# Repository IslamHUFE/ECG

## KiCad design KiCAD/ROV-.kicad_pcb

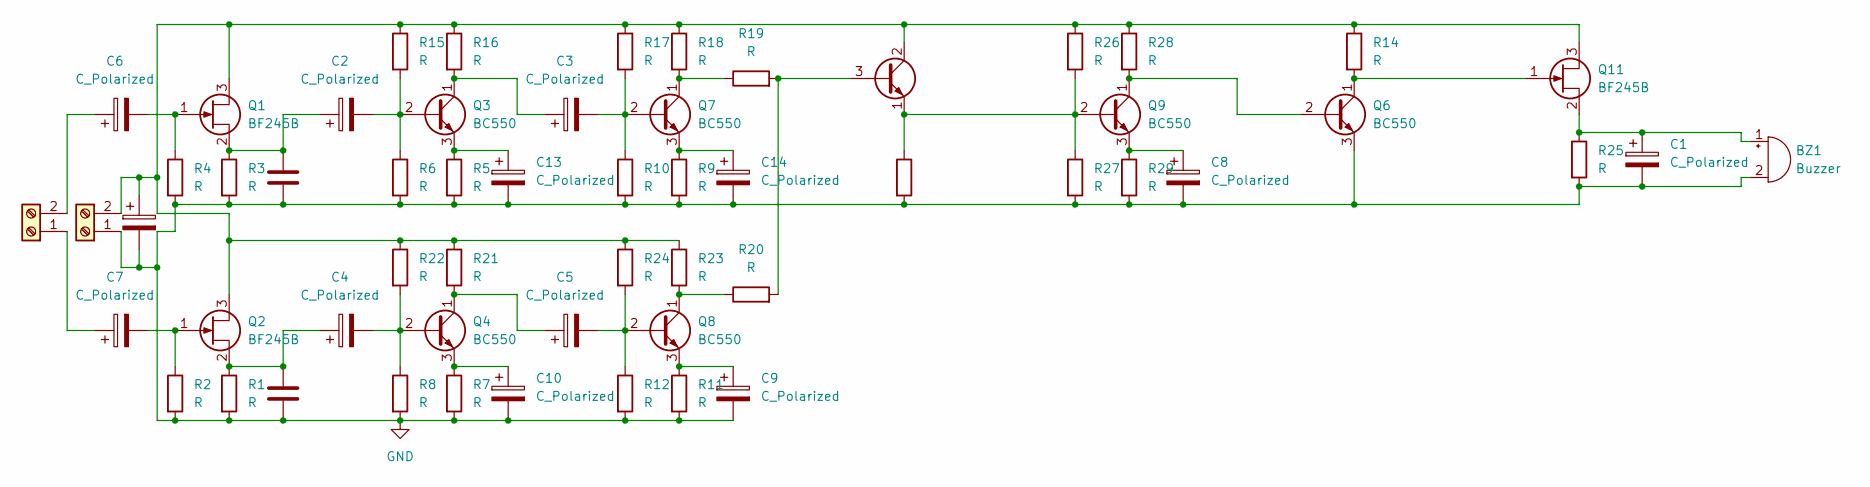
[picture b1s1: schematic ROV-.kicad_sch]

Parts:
BZ1: Buzzer; Buzzer_TDK_PS1240P02BT_D12.2mm_H6.5mm
C1, C2, C3, C4, C5, C6, C7, C8, C9, C10, C13, C14, C15: C_Polarized; CP_Radial_D5.0mm_P2.50mm
C11, C12: C; C_Disc_D3.0mm_W1.6mm_P2.50mm
J1, J2: Screw_Terminal_01x02; TerminalBlock_MaiXu_MX126-5.0-02P_1x02_P5.00mm
Q1, Q2, Q11: BF245B; TO-92_Inline
Q3, Q4, Q6, Q7, Q8, Q9: BC550; TO-92_Inline
Q5: BD139; TO-126-3_Vertical
R1, R2, R3, R4, R5, R6, R7, R8, R9, R10, R11, R12, R13, R14, R15, R16, R17, R18, R19, R20, R21, R22, R23, R24, R25, R26, R27, R28, R29: R; R_Axial_DIN0204_L3.6mm_D1.6mm_P5.08mm_Horizontal

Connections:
GND: BZ1.2 (-), C1.2, C8.2, C9.2, C10.2, C11.2, C12.2, C13.2, C14.2, C15.2, J1.1, Q6.3 (E), R1.2, R2.2, R3.2, R4.2, R5.2, R6.2, R7.2, R8.2, R9.2, R10.2, R11.2, R12.2, R13.2, R25.2, R27.2, R29.2
unnamed: BZ1.1 (+), C1.1, Q11.2 (S), R25.1
unnamed: C15.1, J1.2, Q1.3 (D), Q2.3 (D), Q5.2 (C), Q11.3 (D), R14.1, R15.1, R16.1, R17.1, R18.1, R21.1, R22.1, R23.1, R24.1, R26.1, R28.1
unnamed: C7.1, J2.1
unnamed: C6.1, J2.2
unnamed: C6.2, Q1.1 (G), R4.1
unnamed: C2.1, C12.1, Q1.2 (S), R3.1
unnamed: C7.2, Q2.1 (G), R2.1
unnamed: C4.1, C11.1, Q2.2 (S), R1.1
unnamed: C2.2, Q3.2 (B), R6.1, R15.2
unnamed: C3.1, Q3.1 (C), R16.2
unnamed: C13.1, Q3.3 (E), R5.1
unnamed: C4.2, Q4.2 (B), R8.1, R22.2
unnamed: C5.1, Q4.1 (C), R21.2
unnamed: C10.1, Q4.3 (E), R7.1
unnamed: Q5.3 (B), R19.2, R20.2
unnamed: Q5.1 (E), Q9.2 (B), R13.1, R26.2, R27.1
unnamed: Q6.2 (B), Q9.1 (C), R28.2
unnamed: C3.2, Q7.2 (B), R10.1, R17.2
unnamed: Q7.1 (C), R18.2, R19.1
unnamed: C14.1, Q7.3 (E), R9.1
unnamed: C5.2, Q8.2 (B), R12.1, R24.2
unnamed: Q8.1 (C), R20.1, R23.2
unnamed: C9.1, Q8.3 (E), R11.1
unnamed: C8.1, Q9.3 (E), R29.1
unnamed: Q6.1 (C), Q11.1 (G), R14.2

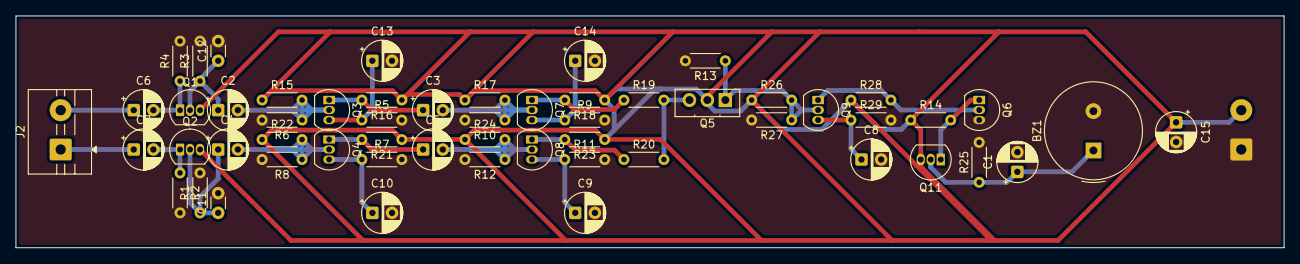
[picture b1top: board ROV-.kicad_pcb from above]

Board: 2 copper layers, 161.2 x 29.5 mm, 57 parts (1 on the bottom side), 26 nets.

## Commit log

2026-04-27 intial commit
2026-05-03 refresh
2026-05-08 LICENSE
2026-05-08 Add LICENSE file
2026-05-22 Change artifact upload path for GitHub Pages
